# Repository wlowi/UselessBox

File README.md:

# A useless box.

Arduino code: UselessBox/UselexxBox.ino

Aufbauanleitung: doc/UselessBox.pdf

Fräsdatei: dxf/UselessBox.dxf

KiCAD Schaltplan und Platinenlayout: KiCAD/UselessBox

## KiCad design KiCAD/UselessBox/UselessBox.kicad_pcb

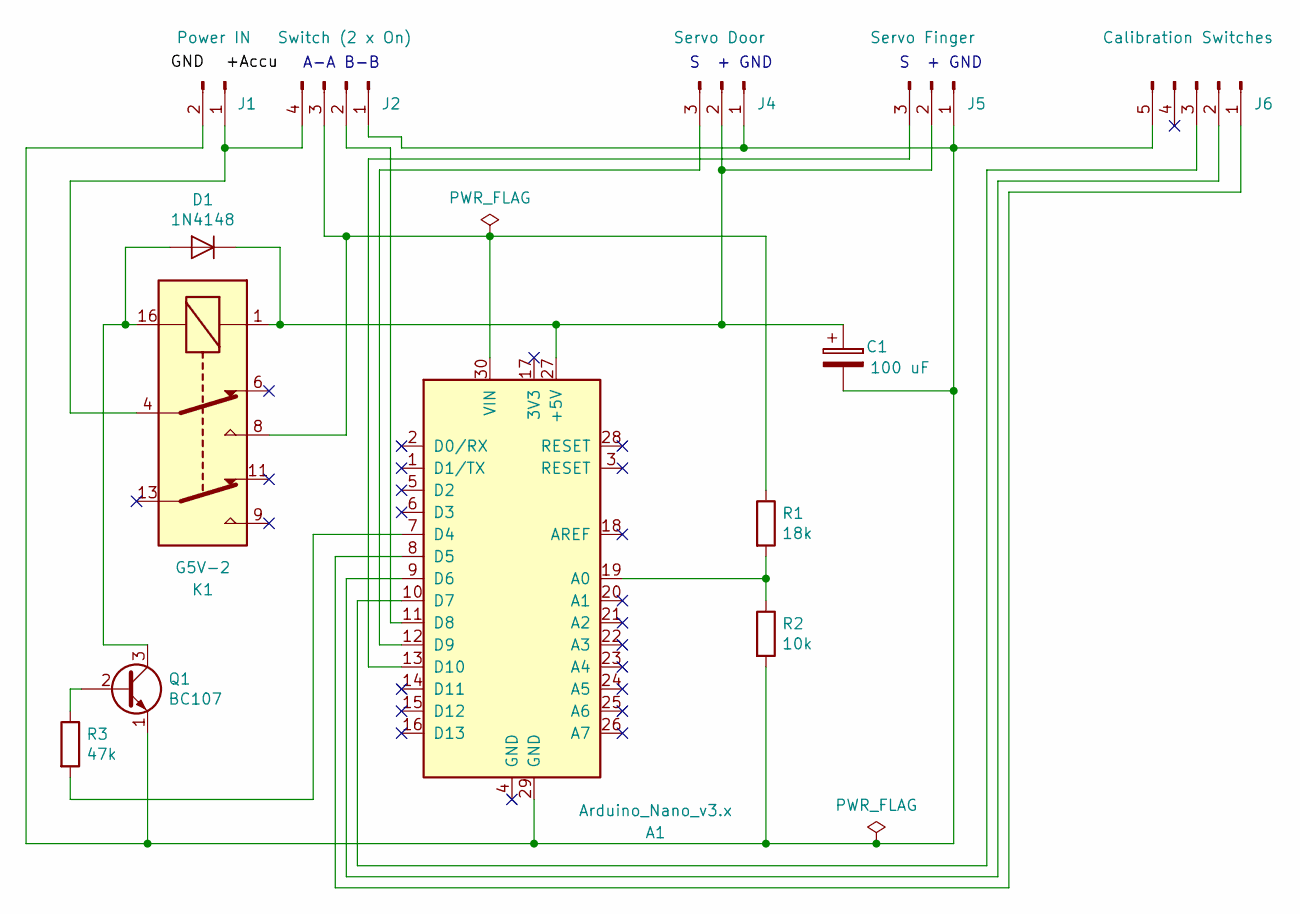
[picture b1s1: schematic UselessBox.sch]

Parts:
A1: Arduino_Nano_v3.x; Arduino_Nano
C1: 100 uF; CP_Radial_D6.3mm_P2.50mm
D1: 1N4148; D_DO-35_SOD27_P7.62mm_Horizontal
J1: Power IN; PinHeader_1x02_P2.54mm_Vertical
J2: Switch (2 x On); PinHeader_1x04_P2.54mm_Vertical
J4: Servo Door; PinHeader_1x03_P2.54mm_Vertical
J5: Servo Finger; PinHeader_1x03_P2.54mm_Vertical
J6: Calibration Switches; PinHeader_1x05_P2.54mm_Vertical
K1: G5V-2; Relay_DPDT_Omron_G5V-2
Q1: BC107; TO-18-3
R1: 18k; R_Axial_DIN0204_L3.6mm_D1.6mm_P7.62mm_Horizontal
R2: 10k; R_Axial_DIN0204_L3.6mm_D1.6mm_P7.62mm_Horizontal
R3: 47k; R_Axial_DIN0204_L3.6mm_D1.6mm_P7.62mm_Horizontal

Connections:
unnamed: A1.7 (D4), R3.2
unnamed: A1.8 (D5), J6.1
unnamed: A1.9 (D6), J6.2
unnamed: A1.10 (D7), J6.3
unnamed: A1.11 (D8), J2.2
unnamed: A1.12 (D9), J4.3
unnamed: A1.13 (D10), J5.3
unnamed: A1.19 (A0), R1.2, R2.1
unnamed: A1.27 (+5V), C1.1, D1.1 (K), J4.2, J5.2, K1.1
unnamed: A1.29 (GND), C1.2, J1.2, J2.1, J4.1, J5.1, J6.5, Q1.1 (E), R2.2
unnamed: A1.30 (VIN), J2.3, K1.8, R1.1
unnamed: D1.2 (A), K1.16, Q1.3 (C)
unnamed: J1.1, J2.4, K1.4
unnamed: Q1.2 (B), R3.1

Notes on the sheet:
A-A B-B
S + GND

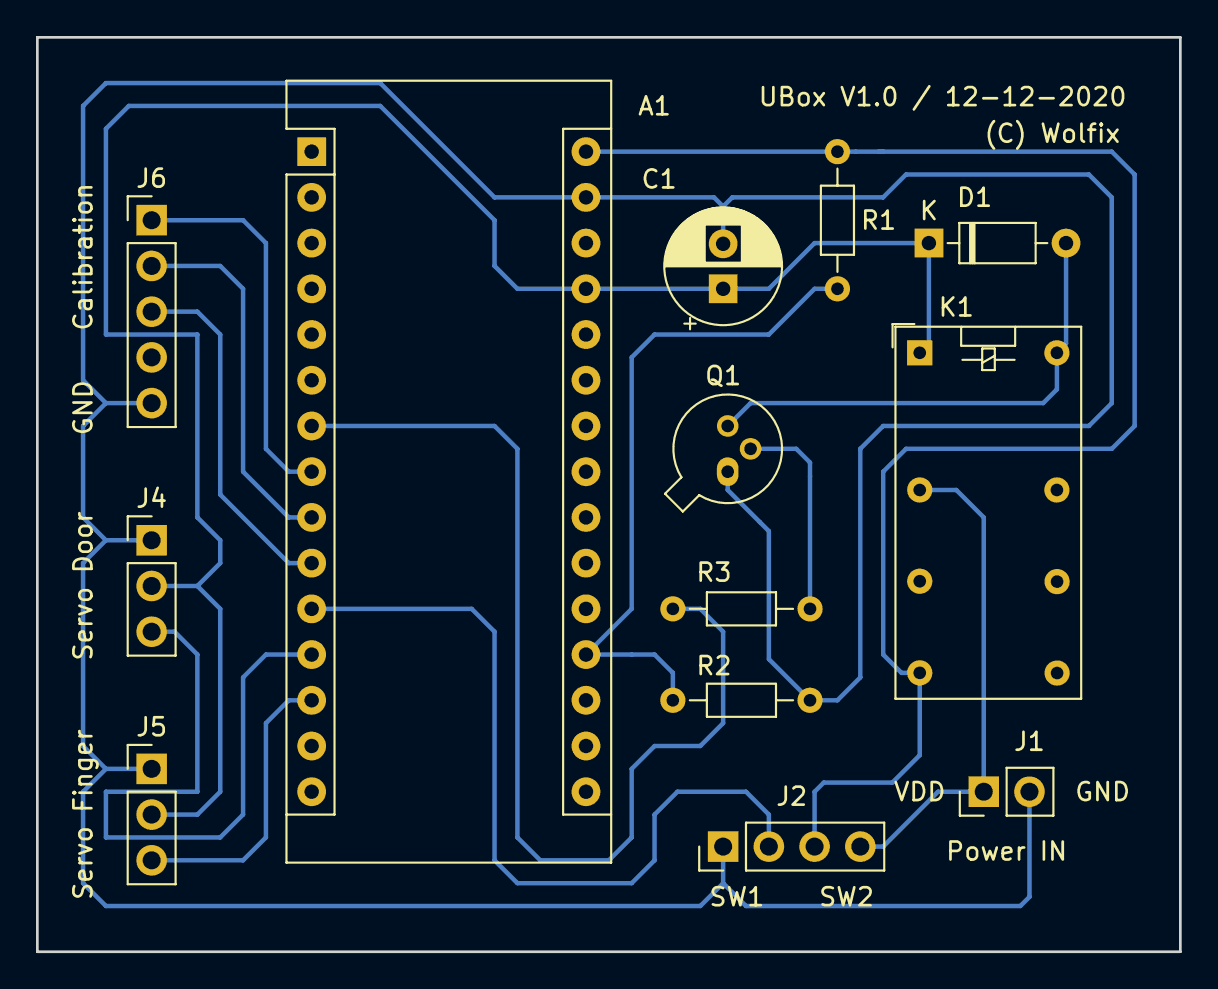
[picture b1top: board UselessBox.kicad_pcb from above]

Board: 2 copper layers, 63.5 x 50.8 mm, 13 parts (0 on the bottom side), 14 nets.

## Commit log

2020-11-28 Creation
2020-11-28 Basically working
2020-11-29 Configuration
2020-12-05 New servo frame time hangling. Immediate response.
2020-12-05 Minor updates
2020-12-11 Added KiCAD
2020-12-12 PCB completed
2020-12-13 Double check and minor fixes
2020-12-18 Correct back mask on PCB
2020-12-19 Low battery monitor.
2020-12-19 Some code refactoring
2020-12-29 Sanitize servo positions. Add PCB images and schema PDF
2021-01-11 Better response to calibration request
2021-03-23 bzr to git migration
2022-02-19 Remove bzrignore add gitignore
2022-12-29 Documentation and dxf added.
